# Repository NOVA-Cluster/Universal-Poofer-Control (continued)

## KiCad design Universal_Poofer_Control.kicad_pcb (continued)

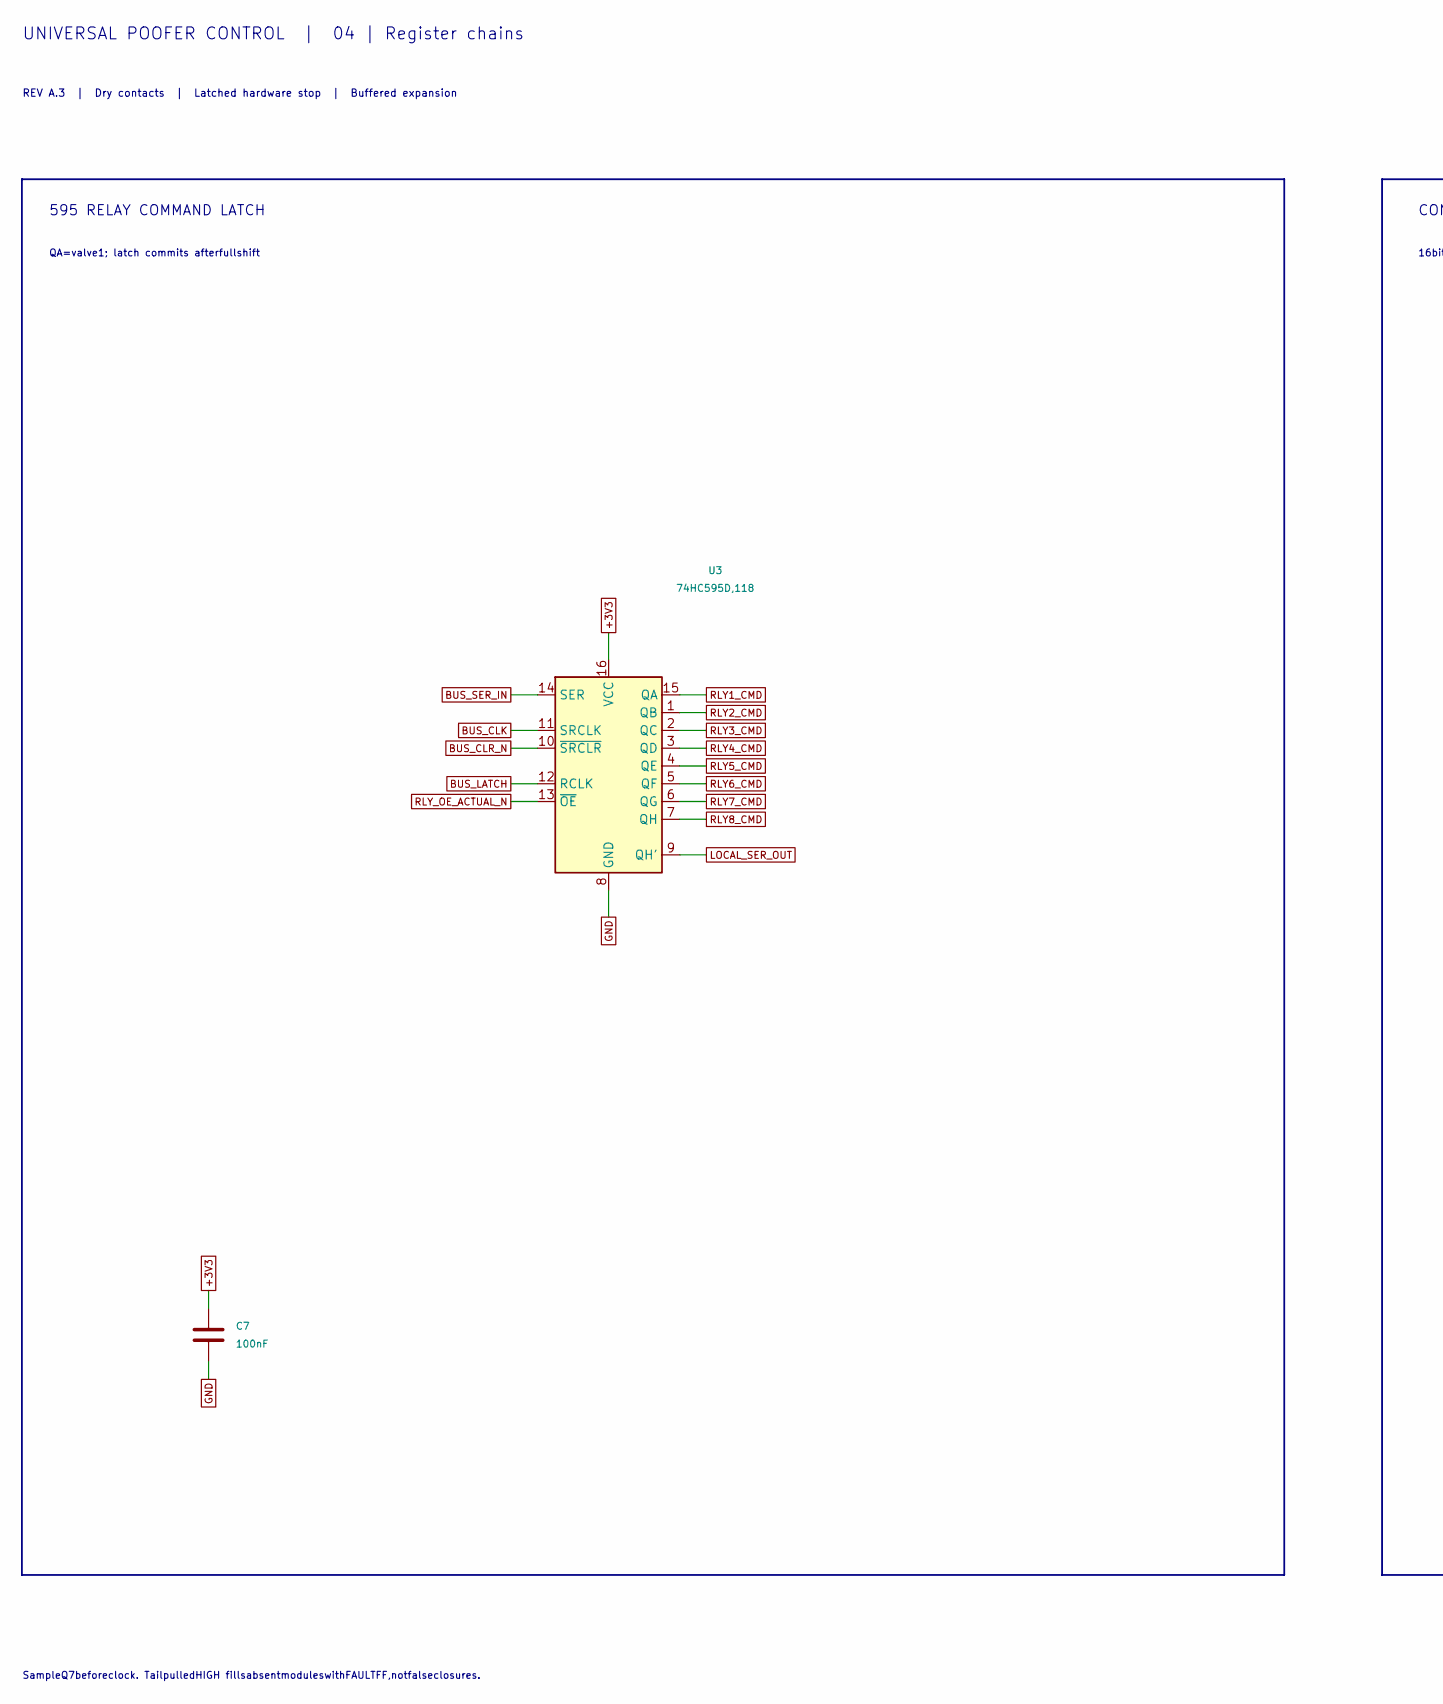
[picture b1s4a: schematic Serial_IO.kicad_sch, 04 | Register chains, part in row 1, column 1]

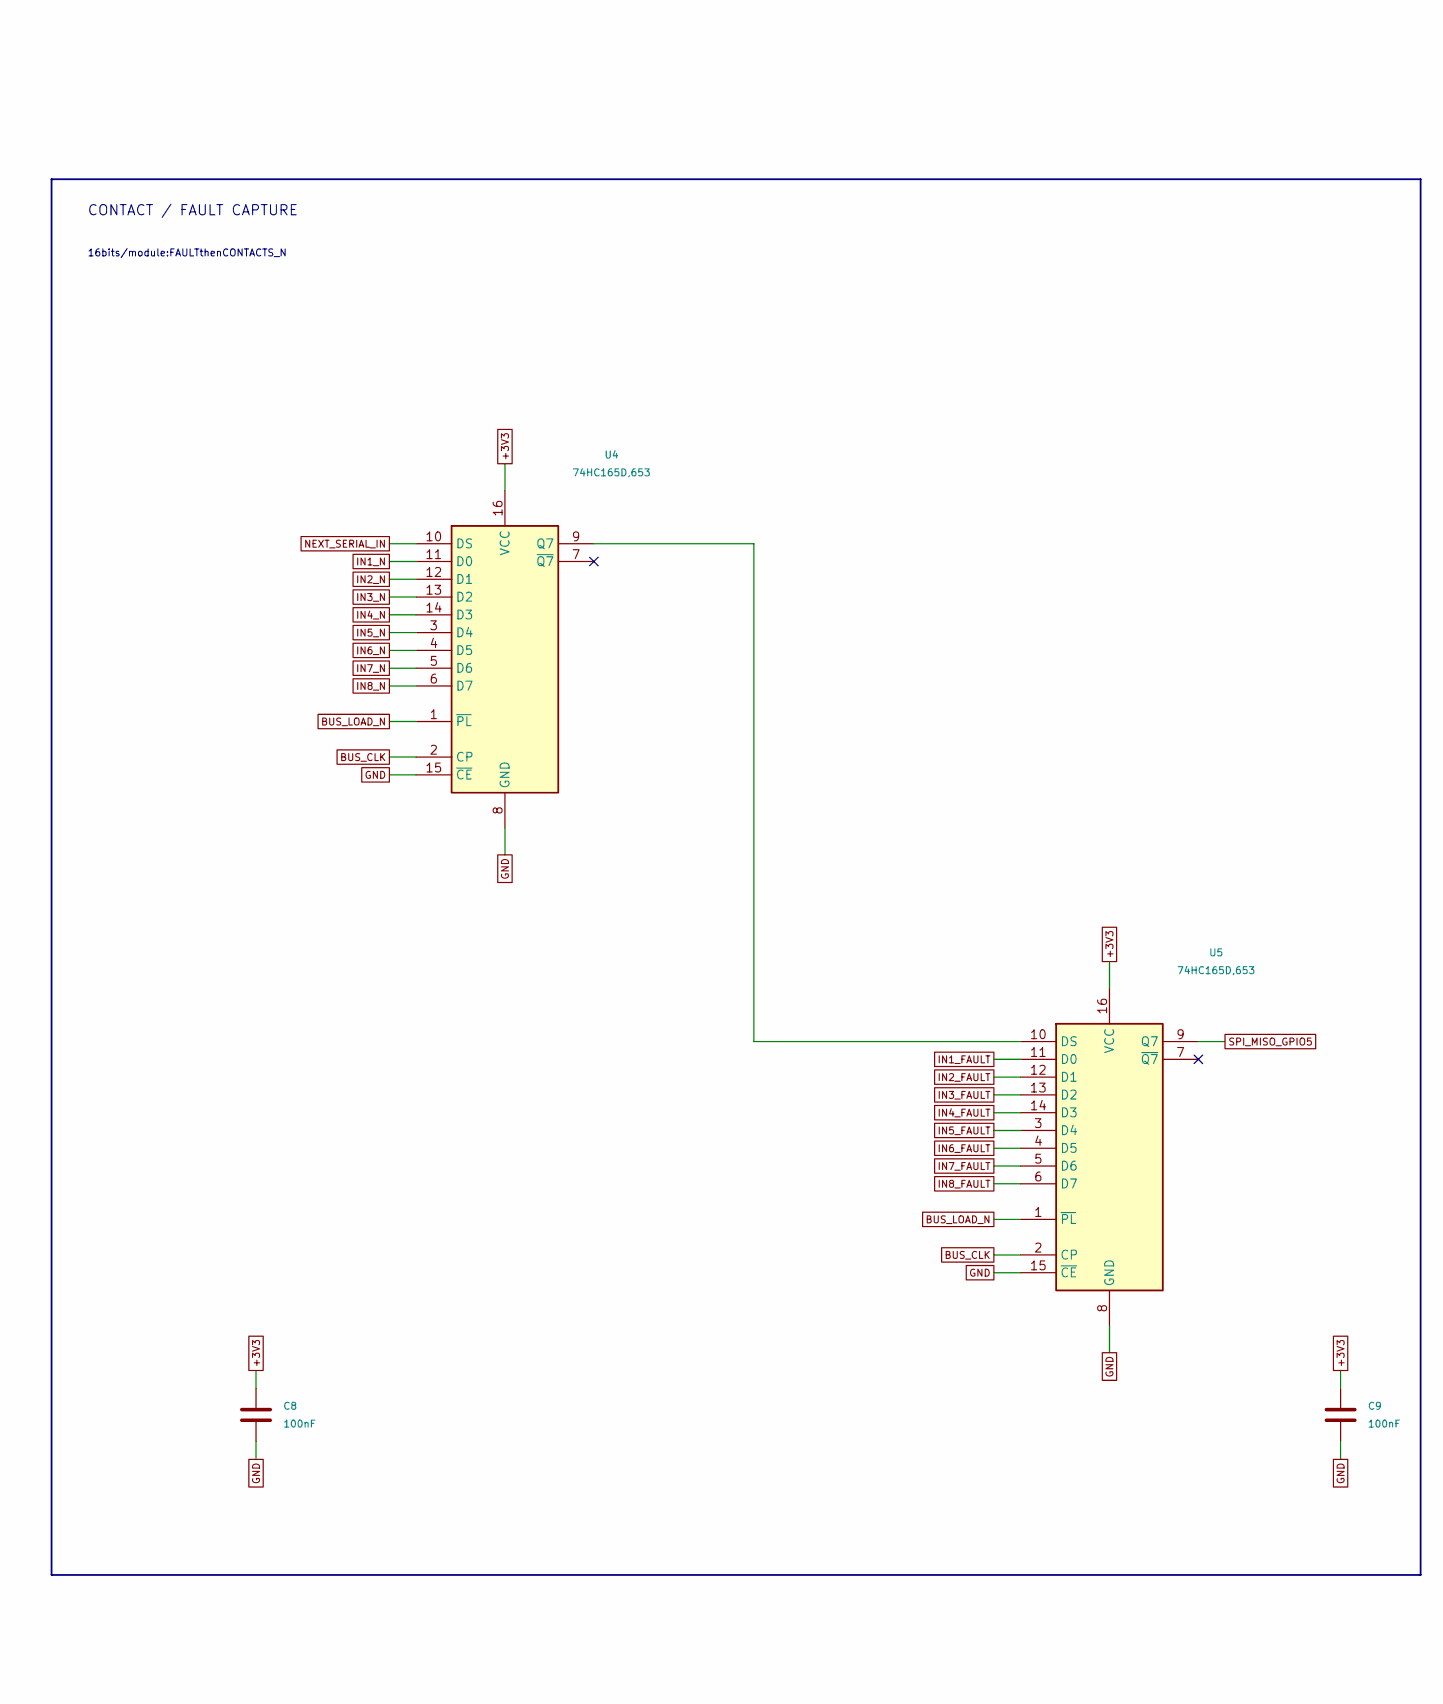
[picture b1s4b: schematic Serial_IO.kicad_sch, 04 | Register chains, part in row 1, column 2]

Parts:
C7, C8, C9: 100nF; C_0805_2012Metric; MPN CC0805KRX7R9BB104; LCSC C49678
U3: 74HC595D,118; SOIC-16_3.9x9.9mm_P1.27mm; MPN 74HC595D,118; LCSC C5947
U4, U5: 74HC165D,653; SOIC-16_3.9x9.9mm_P1.27mm; MPN 74HC165D,653; LCSC C5613

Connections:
+3V3: C7.1, C8.1, C9.1, U3.16 (VCC), U4.16 (VCC), U5.16 (VCC); also elsewhere on the board
BUS_CLK: U3.11 (SRCLK), U4.2 (CP), U5.2 (CP); also elsewhere on the board
BUS_CLR_N: U3.10 (~SRCLR); also elsewhere on the board
BUS_LATCH: U3.12 (RCLK); also elsewhere on the board
BUS_LOAD_N: U4.1 (~PL), U5.1 (~PL); also elsewhere on the board
BUS_SER_IN: U3.14 (SER); also elsewhere on the board
GND: C7.2, C8.2, C9.2, U3.8 (GND), U4.8 (GND), U4.15 (~CE), U5.8 (GND), U5.15 (~CE); also elsewhere on the board
IN1_FAULT: U5.11 (D0); also elsewhere on the board
IN1_N: U4.11 (D0); also elsewhere on the board
IN2_FAULT: U5.12 (D1); also elsewhere on the board
IN2_N: U4.12 (D1); also elsewhere on the board
IN3_FAULT: U5.13 (D2); also elsewhere on the board
IN3_N: U4.13 (D2); also elsewhere on the board
IN4_FAULT: U5.14 (D3); also elsewhere on the board
IN4_N: U4.14 (D3); also elsewhere on the board
IN5_FAULT: U5.3 (D4); also elsewhere on the board
IN5_N: U4.3 (D4); also elsewhere on the board
IN6_FAULT: U5.4 (D5); also elsewhere on the board
IN6_N: U4.4 (D5); also elsewhere on the board
IN7_FAULT: U5.5 (D6); also elsewhere on the board
IN7_N: U4.5 (D6); also elsewhere on the board
IN8_FAULT: U5.6 (D7); also elsewhere on the board
IN8_N: U4.6 (D7); also elsewhere on the board
LOCAL_SER_OUT: U3.9 (QH'); also elsewhere on the board
NEXT_SERIAL_IN: U4.10 (DS); also elsewhere on the board
unnamed: U4.9 (Q7), U5.10 (DS)
RLY1_CMD: U3.15 (QA); also elsewhere on the board
RLY2_CMD: U3.1 (QB); also elsewhere on the board
RLY3_CMD: U3.2 (QC); also elsewhere on the board
RLY4_CMD: U3.3 (QD); also elsewhere on the board
RLY5_CMD: U3.4 (QE); also elsewhere on the board
RLY6_CMD: U3.5 (QF); also elsewhere on the board
RLY7_CMD: U3.6 (QG); also elsewhere on the board
RLY8_CMD: U3.7 (QH); also elsewhere on the board
RLY_OE_ACTUAL_N: U3.13 (~OE); also elsewhere on the board
SPI_MISO_GPIO5: U5.9 (Q7); also elsewhere on the board

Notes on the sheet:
UNIVERSAL POOFER CONTROL | 04 | Register chains
REV A.3 | Dry contacts | Latched hardware stop | Buffered expansion
595 RELAY COMMAND LATCH
QA=valve1; latch commits afterfullshift
CONTACT / FAULT CAPTURE
16bits/module:FAULTthenCONTACTS_N
SampleQ7beforeclock. TailpulledHIGH fillsabsentmoduleswithFAULTFF,notfalseclosures.

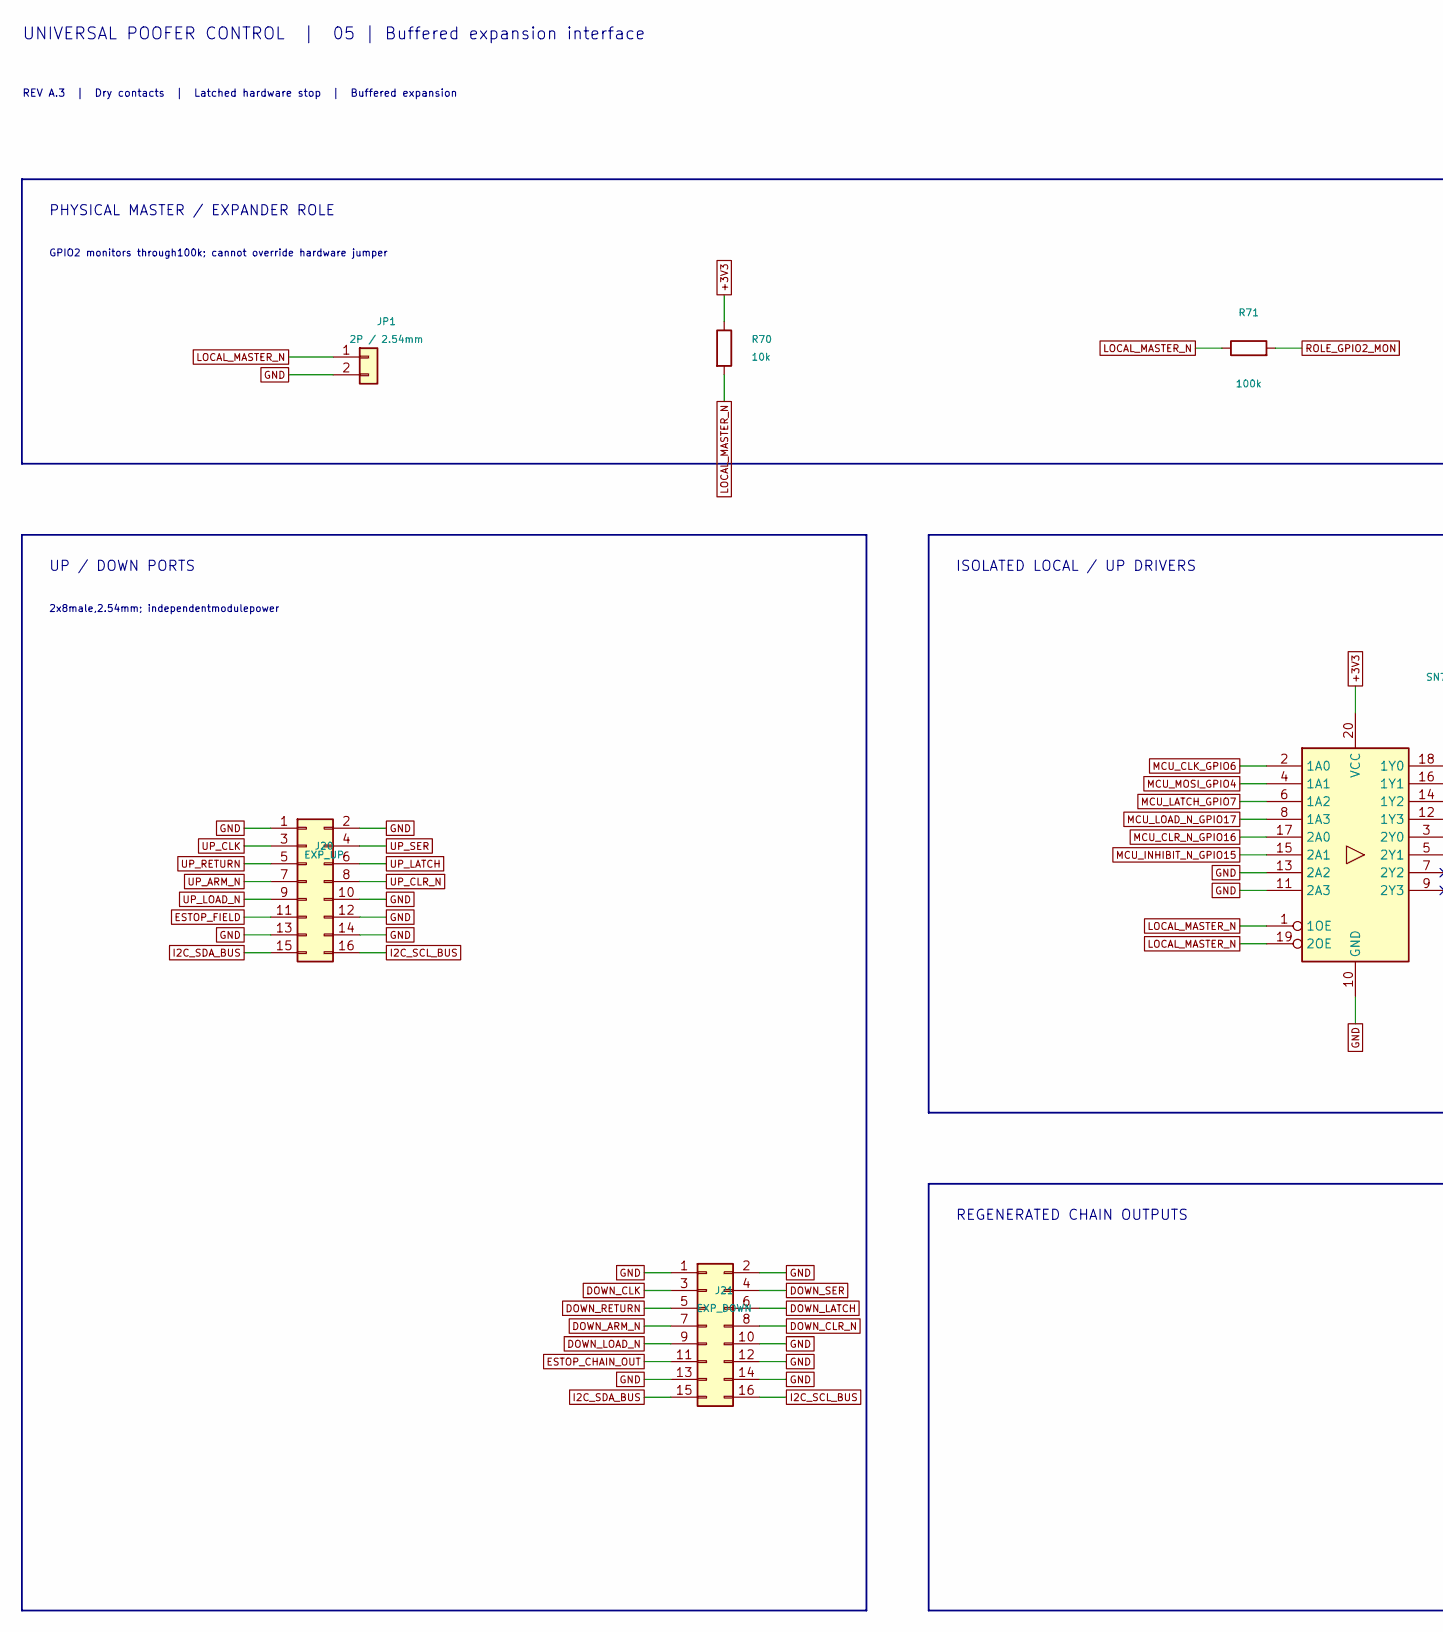
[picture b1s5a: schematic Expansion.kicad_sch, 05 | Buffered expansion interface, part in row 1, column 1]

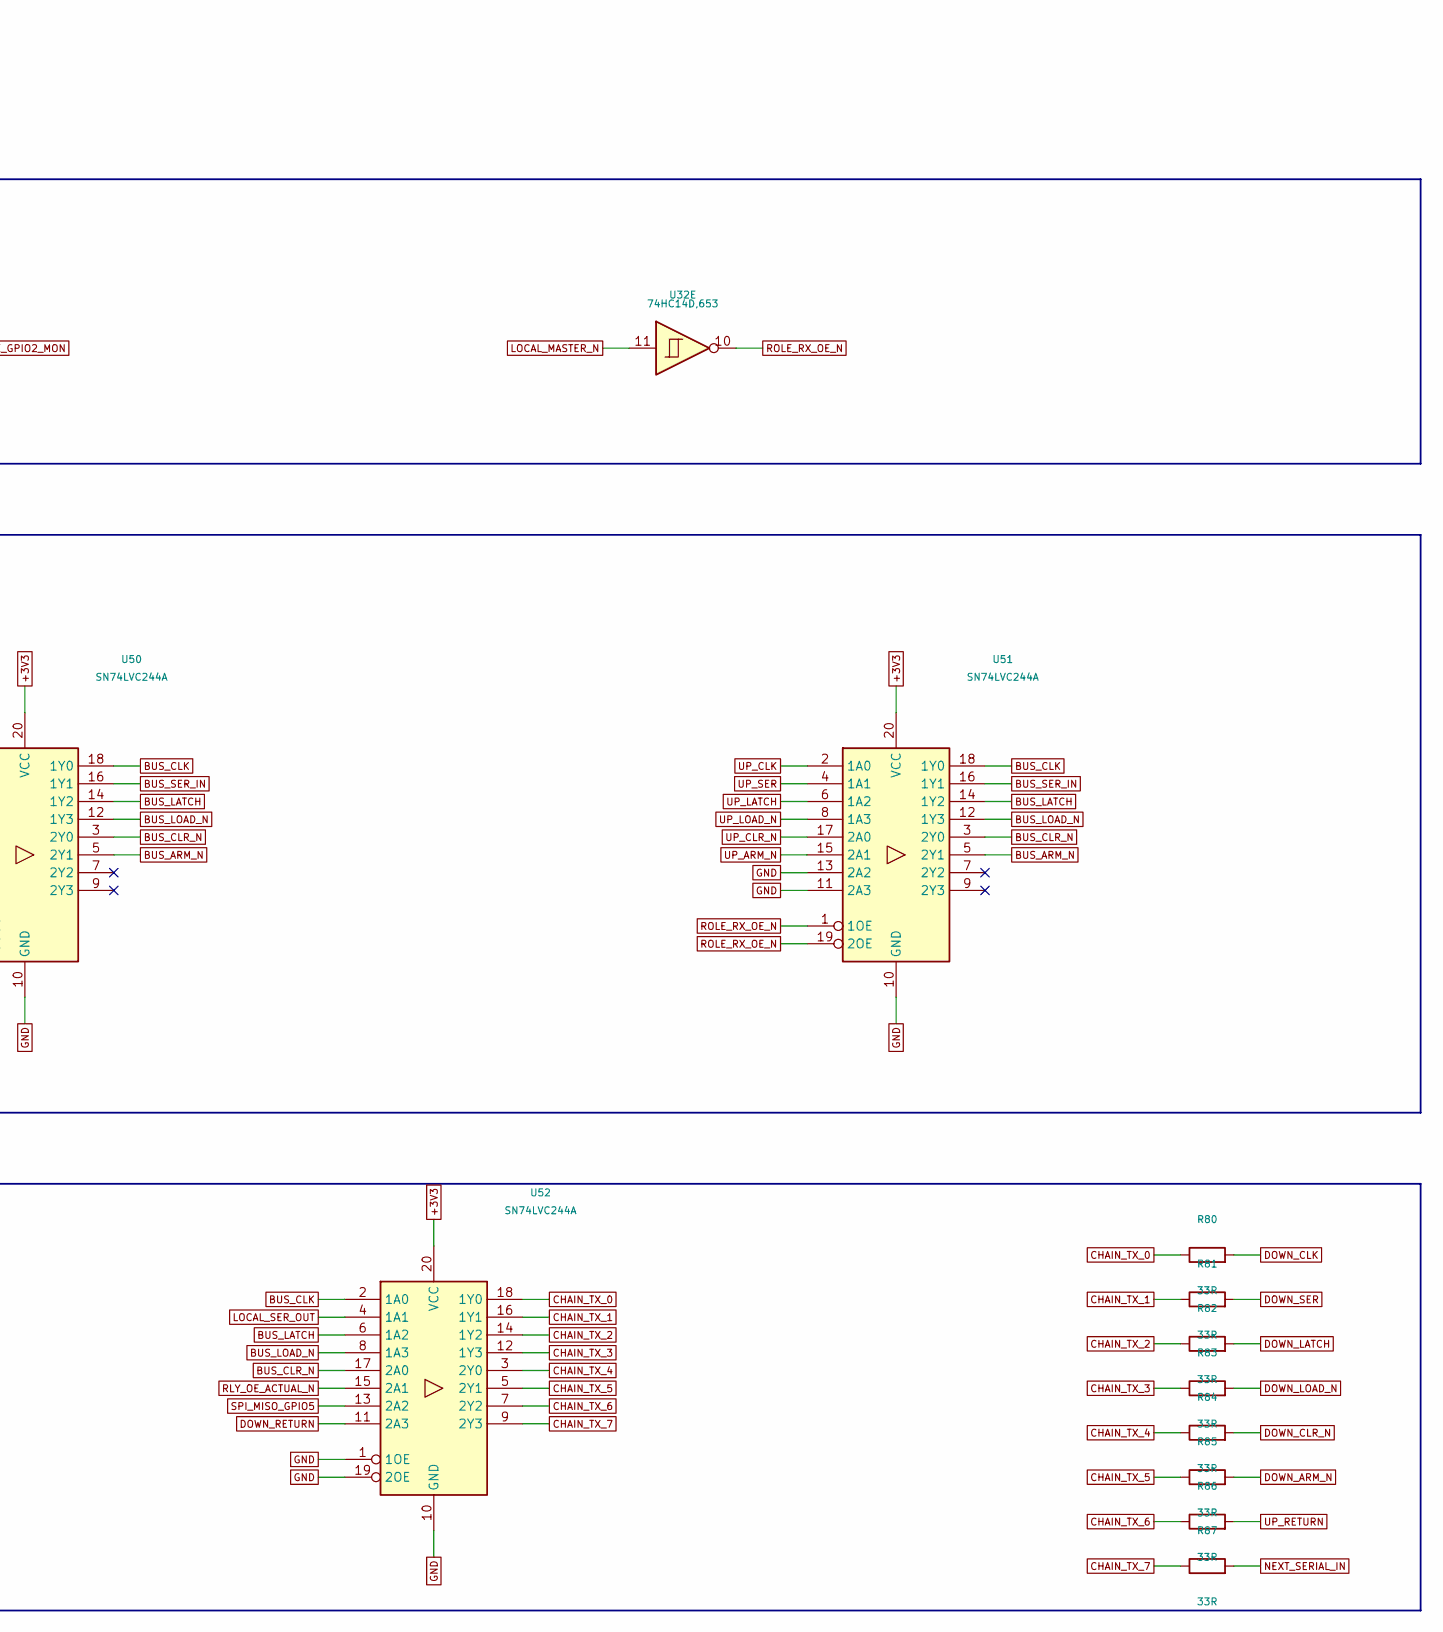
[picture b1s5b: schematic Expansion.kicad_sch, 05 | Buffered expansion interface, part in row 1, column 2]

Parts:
J20: EXP_UP; PinHeader_2x08_P2.54mm_Vertical; MPN 2.54-2*8P针; LCSC C68234
J21: EXP_DOWN; PinHeader_2x08_P2.54mm_Vertical; MPN 2.54-2*8P针; LCSC C68234
JP1: 2P / 2.54mm; PinHeader_1x02_P2.54mm_Vertical; MPN B-2100S02P-A110; LCSC C124375
R70: 10k; R_0805_2012Metric; MPN 0805W8F1002T5E; LCSC C17414
R71: 100k; R_0805_2012Metric; MPN 0805W8F1003T5E; LCSC C149504
R80, R81, R82, R83, R84, R85, R86, R87: 33R; R_0805_2012Metric; MPN 0805W8F330JT5E; LCSC C17634
U32: 74HC14D,653; SOIC-14_3.9x8.7mm_P1.27mm; MPN 74HC14D,653; LCSC C5605
U50, U51, U52: SN74LVC244A; SOIC-20W_7.5x12.8mm_P1.27mm; MPN SN74LVC244ADWR; LCSC C507250

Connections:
+3V3: R70.1, U50.20 (VCC), U51.20 (VCC), U52.20 (VCC); also elsewhere on the board
BUS_ARM_N: U50.5 (2Y1), U51.5 (2Y1); also elsewhere on the board
BUS_CLK: U50.18 (1Y0), U51.18 (1Y0), U52.2 (1A0); also elsewhere on the board
BUS_CLR_N: U50.3 (2Y0), U51.3 (2Y0), U52.17 (2A0); also elsewhere on the board
BUS_LATCH: U50.14 (1Y2), U51.14 (1Y2), U52.6 (1A2); also elsewhere on the board
BUS_LOAD_N: U50.12 (1Y3), U51.12 (1Y3), U52.8 (1A3); also elsewhere on the board
BUS_SER_IN: U50.16 (1Y1), U51.16 (1Y1); also elsewhere on the board
CHAIN_TX_0: R80.1, U52.18 (1Y0)
CHAIN_TX_1: R81.1, U52.16 (1Y1)
CHAIN_TX_2: R82.1, U52.14 (1Y2)
CHAIN_TX_3: R83.1, U52.12 (1Y3)
CHAIN_TX_4: R84.1, U52.3 (2Y0)
CHAIN_TX_5: R85.1, U52.5 (2Y1)
CHAIN_TX_6: R86.1, U52.7 (2Y2)
CHAIN_TX_7: R87.1, U52.9 (2Y3)
DOWN_ARM_N: J21.7, R85.2
DOWN_CLK: J21.3, R80.2
DOWN_CLR_N: J21.8, R84.2
DOWN_LATCH: J21.6, R82.2
DOWN_LOAD_N: J21.9, R83.2
DOWN_RETURN: J21.5, U52.11 (2A3); also elsewhere on the board
DOWN_SER: J21.4, R81.2
ESTOP_CHAIN_OUT: J21.11; also elsewhere on the board
ESTOP_FIELD: J20.11; also elsewhere on the board
GND: J20.1, J20.2, J20.10, J20.12, J20.13, J20.14, J21.1, J21.2, J21.10, J21.12, J21.13, J21.14, JP1.2, U50.10 (GND), U50.11 (2A3), U50.13 (2A2), U51.10 (GND), U51.11 (2A3), U51.13 (2A2), U52.1 (1OE), U52.10 (GND), U52.19 (2OE); also elsewhere on the board
I2C_SCL_BUS: J20.16, J21.16; also elsewhere on the board
I2C_SDA_BUS: J20.15, J21.15; also elsewhere on the board
LOCAL_MASTER_N: JP1.1, R70.2, R71.1, U32.11, U50.1 (1OE), U50.19 (2OE); also elsewhere on the board
LOCAL_SER_OUT: U52.4 (1A1); also elsewhere on the board
MCU_CLK_GPIO6: U50.2 (1A0); also elsewhere on the board
MCU_CLR_N_GPIO16: U50.17 (2A0); also elsewhere on the board
MCU_INHIBIT_N_GPIO15: U50.15 (2A1); also elsewhere on the board
MCU_LATCH_GPIO7: U50.6 (1A2); also elsewhere on the board
MCU_LOAD_N_GPIO17: U50.8 (1A3); also elsewhere on the board
MCU_MOSI_GPIO4: U50.4 (1A1); also elsewhere on the board
NEXT_SERIAL_IN: R87.2; also elsewhere on the board
RLY_OE_ACTUAL_N: U52.15 (2A1); also elsewhere on the board
ROLE_GPIO2_MON: R71.2; also elsewhere on the board
ROLE_RX_OE_N: U32.10, U51.1 (1OE), U51.19 (2OE)
SPI_MISO_GPIO5: U52.13 (2A2); also elsewhere on the board
UP_ARM_N: J20.7, U51.15 (2A1); also elsewhere on the board
UP_CLK: J20.3, U51.2 (1A0); also elsewhere on the board
UP_CLR_N: J20.8, U51.17 (2A0); also elsewhere on the board
UP_LATCH: J20.6, U51.6 (1A2); also elsewhere on the board
UP_LOAD_N: J20.9, U51.8 (1A3); also elsewhere on the board
UP_RETURN: J20.5, R86.2
UP_SER: J20.4, U51.4 (1A1); also elsewhere on the board

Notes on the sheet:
UNIVERSAL POOFER CONTROL | 05 | Buffered expansion interface
REV A.3 | Dry contacts | Latched hardware stop | Buffered expansion
PHYSICAL MASTER / EXPANDER ROLE
GPIO2 monitors through100k; cannot override hardware jumper
UP / DOWN PORTS
2x8male,2.54mm; independentmodulepower
ISOLATED LOCAL / UP DRIVERS
REGENERATED CHAIN OUTPUTS

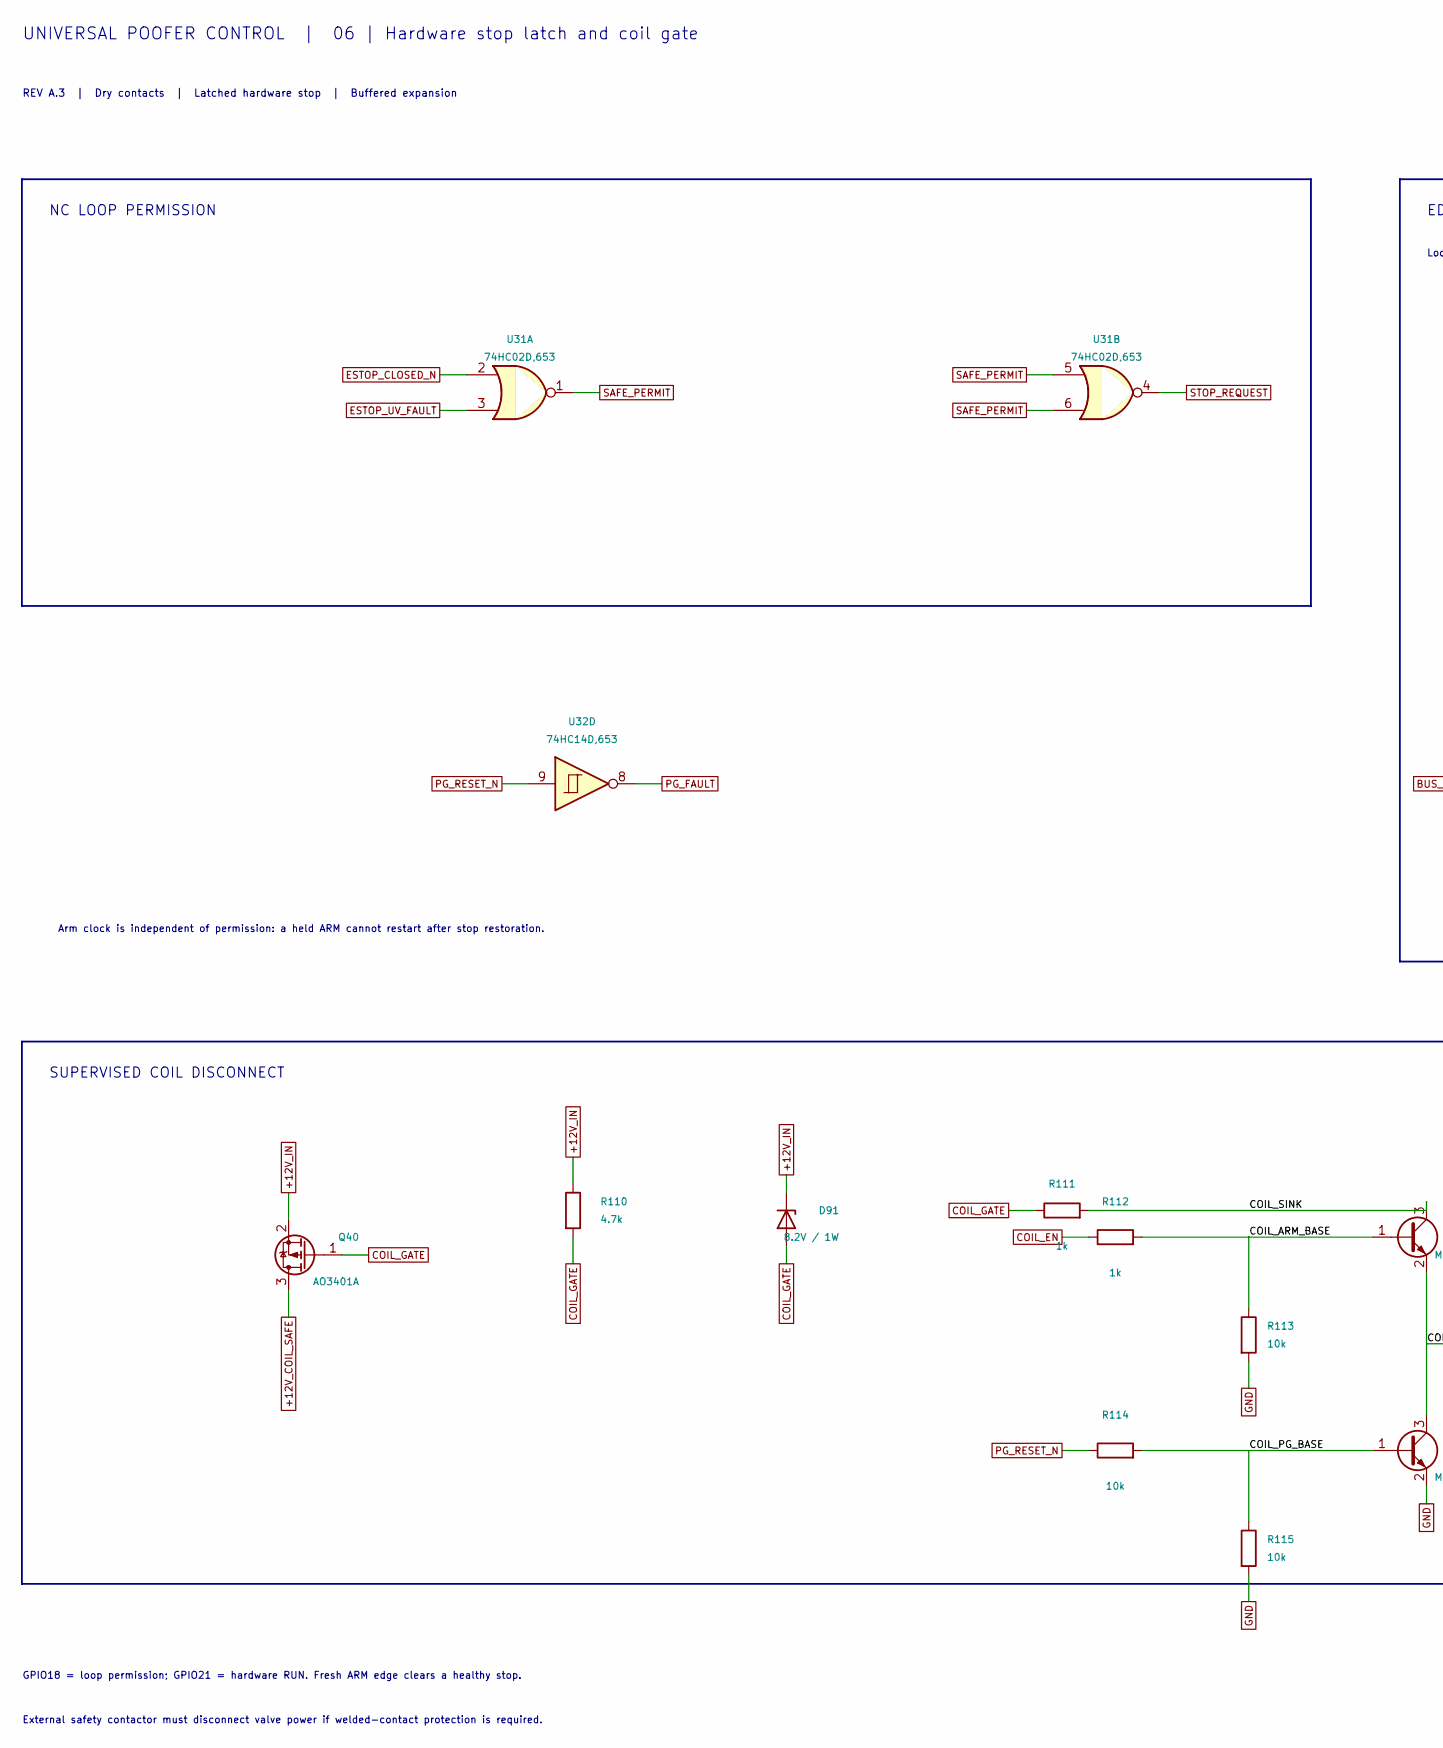
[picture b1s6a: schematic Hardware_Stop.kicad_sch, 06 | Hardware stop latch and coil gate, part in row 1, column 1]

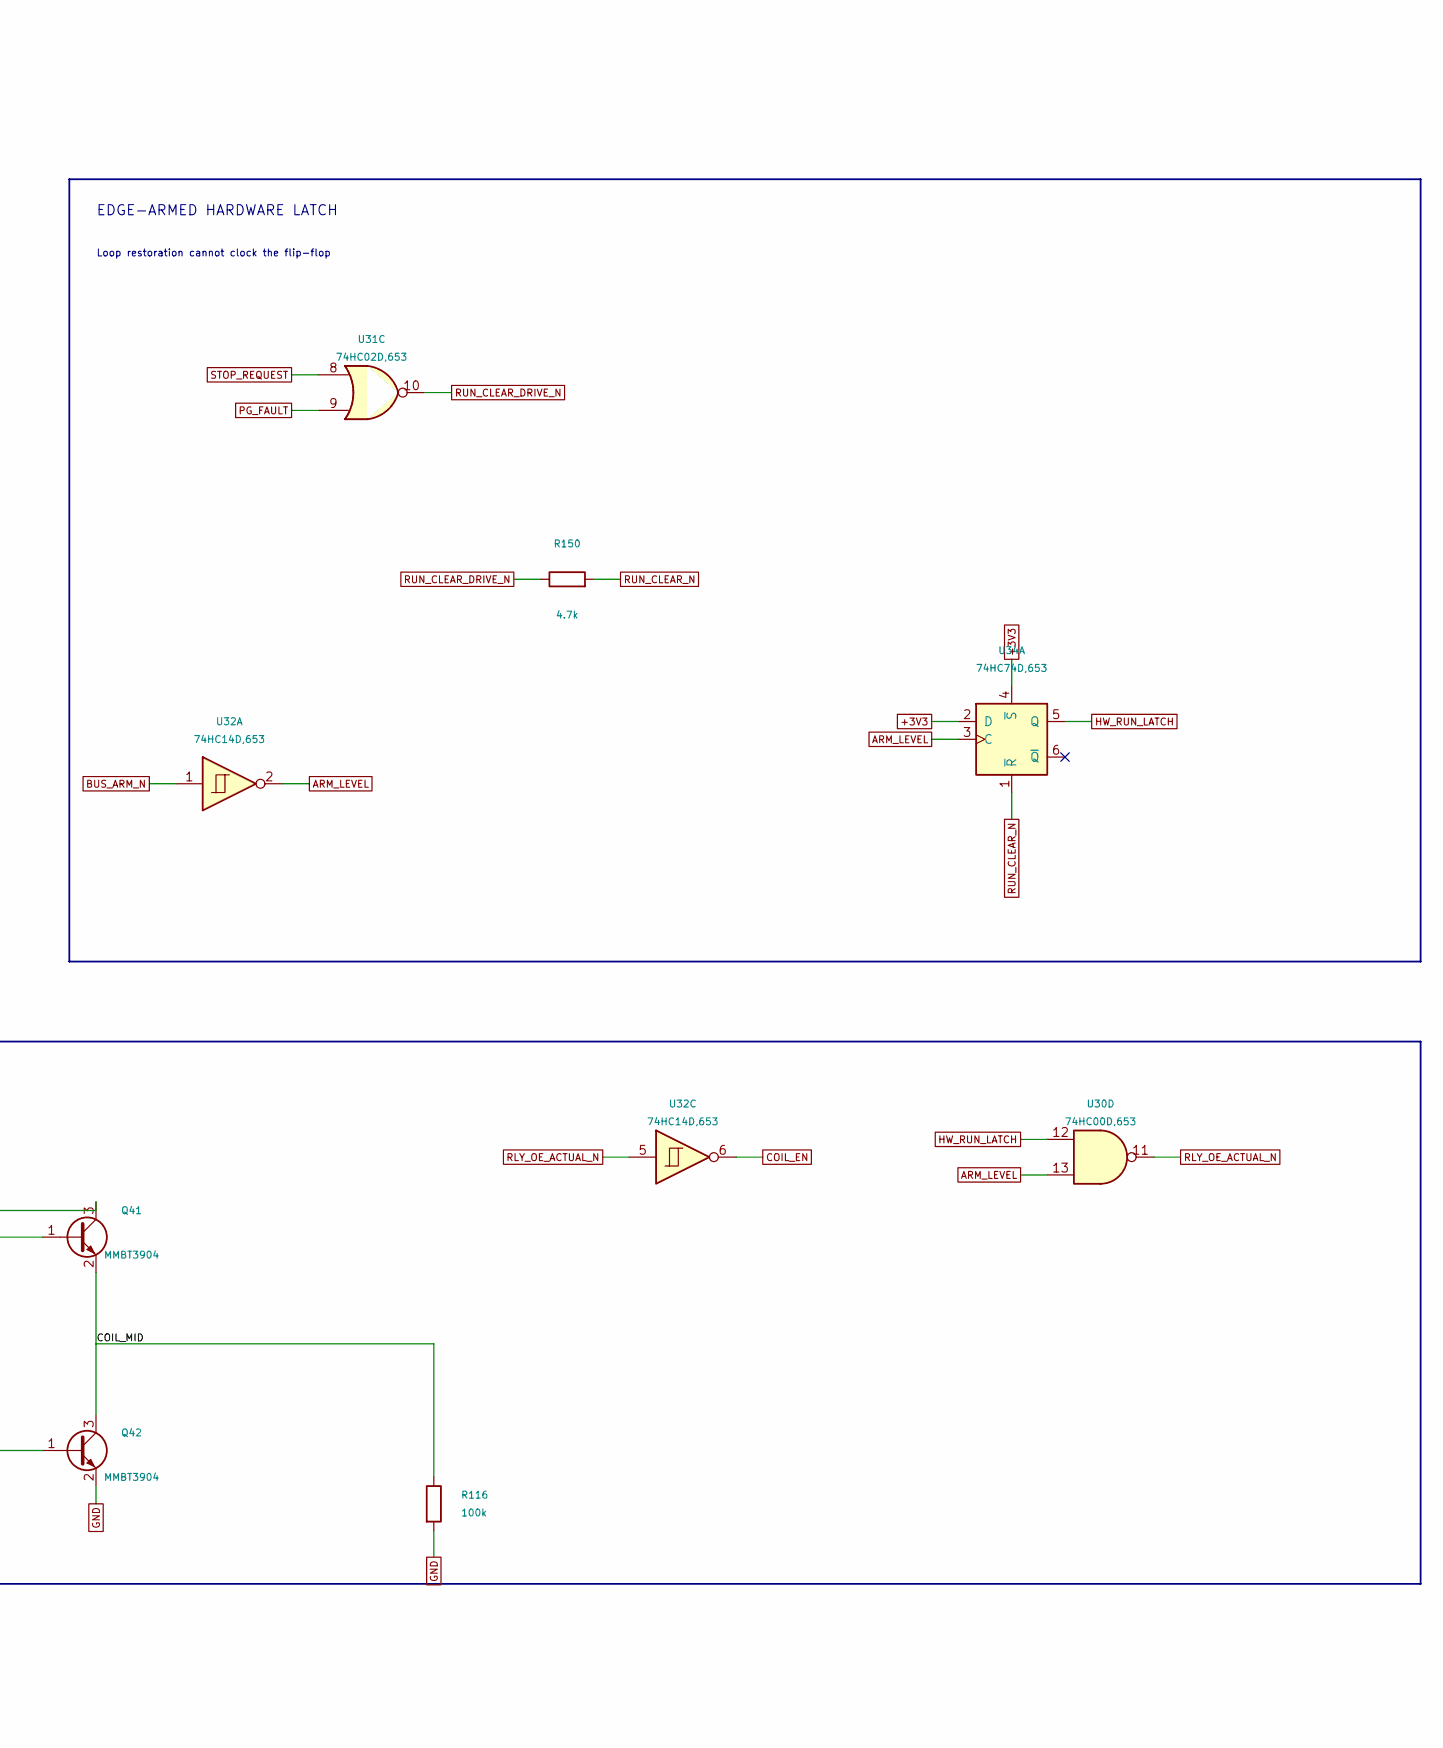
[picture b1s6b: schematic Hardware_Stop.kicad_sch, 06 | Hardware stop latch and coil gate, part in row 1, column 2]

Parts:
D91: 8.2V / 1W; D_SMA; MPN SMAZ8V2-13-F; LCSC C84362
Q40: AO3401A; SOT-23; MPN AO3401A; LCSC C15127
Q41, Q42: MMBT3904; SOT-23; MPN MMBT3904(RANGE:100-300); LCSC C20526
R110, R150: 4.7k; R_0805_2012Metric; MPN 0805W8F4701T5E; LCSC C17673
R111, R112: 1k; R_0805_2012Metric; MPN 0805W8F1001T5E; LCSC C17513
R113, R114, R115: 10k; R_0805_2012Metric; MPN 0805W8F1002T5E; LCSC C17414
R116: 100k; R_0805_2012Metric; MPN 0805W8F1003T5E; LCSC C149504
U30: 74HC00D,653; SOIC-14_3.9x8.7mm_P1.27mm; MPN 74HC00D,653; LCSC C5586
U31: 74HC02D,653; SOIC-14_3.9x8.7mm_P1.27mm; MPN 74HC02D,653; LCSC C5588
U32: 74HC14D,653; SOIC-14_3.9x8.7mm_P1.27mm; MPN 74HC14D,653; LCSC C5605
U34: 74HC74D,653; SOIC-14_3.9x8.7mm_P1.27mm; MPN 74HC74D,653; LCSC C27597

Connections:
+3V3: U34.2 (D), U34.4 (~S); also elsewhere on the board
+12V_COIL_SAFE: Q40.3 (D); also elsewhere on the board
+12V_IN: D91.1 (K), Q40.2 (S), R110.1; also elsewhere on the board
/06 | Hardware stop latch and coil gate/COIL_ARM_BASE: Q41.1 (B), R112.2, R113.1
/06 | Hardware stop latch and coil gate/COIL_MID: Q41.2 (E), Q42.3 (C), R116.1
/06 | Hardware stop latch and coil gate/COIL_PG_BASE: Q42.1 (B), R114.2, R115.1
/06 | Hardware stop latch and coil gate/COIL_SINK: Q41.3 (C), R111.2
ARM_LEVEL: U30.13, U32.2, U34.3 (C)
BUS_ARM_N: U32.1; also elsewhere on the board
COIL_EN: R112.1, U32.6
COIL_GATE: D91.2 (A), Q40.1 (G), R110.2, R111.1
ESTOP_CLOSED_N: U31.2; also elsewhere on the board
ESTOP_UV_FAULT: U31.3; also elsewhere on the board
GND: Q42.2 (E), R113.2, R115.2, R116.2; also elsewhere on the board
HW_RUN_LATCH: U30.12, U34.5 (Q); also elsewhere on the board
PG_FAULT: U31.9, U32.8
PG_RESET_N: R114.1, U32.9; also elsewhere on the board
RLY_OE_ACTUAL_N: U30.11, U32.5; also elsewhere on the board
RUN_CLEAR_DRIVE_N: R150.1, U31.10
RUN_CLEAR_N: R150.2, U34.1 (~R); also elsewhere on the board
SAFE_PERMIT: U31.1, U31.5, U31.6; also elsewhere on the board
STOP_REQUEST: U31.4, U31.8

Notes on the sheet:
UNIVERSAL POOFER CONTROL | 06 | Hardware stop latch and coil gate
REV A.3 | Dry contacts | Latched hardware stop | Buffered expansion
NC LOOP PERMISSION
EDGE-ARMED HARDWARE LATCH
Loop restoration cannot clock the flip-flop
SUPERVISED COIL DISCONNECT
Arm clock is independent of permission: a held ARM cannot restart after stop restoration.
GPIO18 = loop permission; GPIO21 = hardware RUN. Fresh ARM edge clears a healthy stop.
External safety contactor must disconnect valve power if welded-contact protection is required.
